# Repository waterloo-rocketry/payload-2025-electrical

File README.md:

2025 Payload Electrical Design
==============================

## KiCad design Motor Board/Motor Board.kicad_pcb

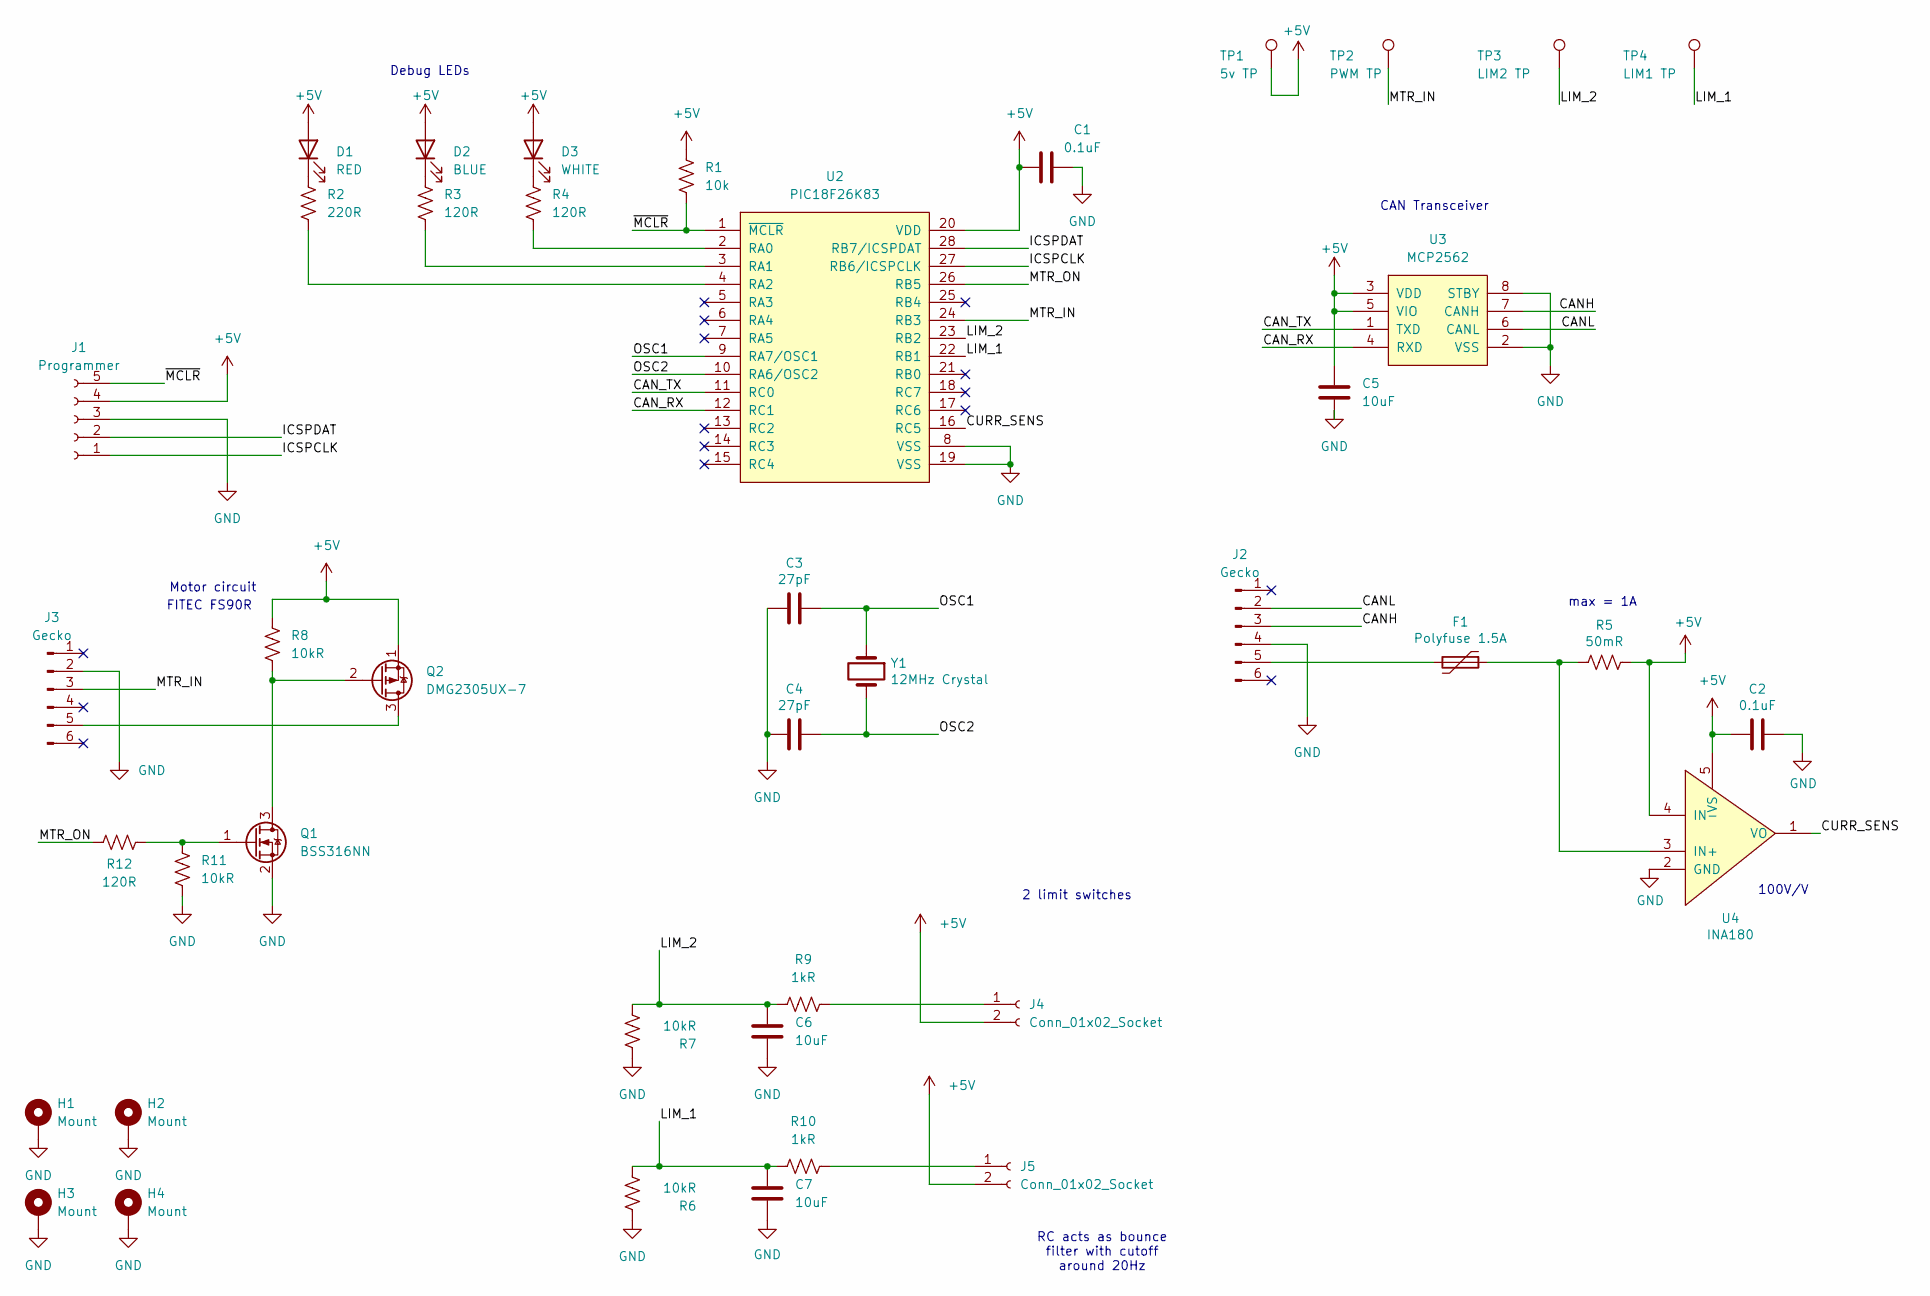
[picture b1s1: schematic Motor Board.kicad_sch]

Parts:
C1, C2: 0.1uF; C_0805_2012Metric_Pad1.18x1.45mm_HandSolder
C3, C4: 27pF; C_0805_2012Metric_Pad1.18x1.45mm_HandSolder; DigiKey 1276-2622-1-ND
C5, C6, C7: 10uF; C_0805_2012Metric_Pad1.18x1.45mm_HandSolder
D1: RED; LED_1206_3216Metric_Pad1.42x1.75mm_HandSolder
D2: BLUE; LED_1206_3216Metric_Pad1.42x1.75mm_HandSolder
D3: WHITE; LED_1206_3216Metric_Pad1.42x1.75mm_HandSolder
F1: Polyfuse 1.5A; Fuse_1206_3216Metric_Pad1.42x1.75mm_HandSolder
H1, H2, H3, H4: Mount; MountingHole_3.2mm_M3_Pad
J1: Programmer; PinSocket_5x2.54_SMD_90deg_952-3198-1-ND
J2, J3: Gecko; connector_Harwin_G125–MG10605M4P
J4, J5: Conn_01x02_Socket; JST_PH_S2B-PH-K_1x02_P2.00mm_Horizontal
Q1: BSS316NN; SOT-323_SC-70_Handsoldering
Q2: DMG2305UX-7; SOT-23
R1: 10k; R_0805_2012Metric_Pad1.20x1.40mm_HandSolder
R2: 220R; R_0805_2012Metric_Pad1.20x1.40mm_HandSolder
R3, R4, R12: 120R; R_0805_2012Metric_Pad1.20x1.40mm_HandSolder
R5: 50mR; R_0805_2012Metric_Pad1.20x1.40mm_HandSolder
R6, R7, R8, R11: 10kR; R_0805_2012Metric_Pad1.20x1.40mm_HandSolder
R9, R10: 1kR; R_0805_2012Metric_Pad1.20x1.40mm_HandSolder
TP1: 5v TP; TestPoint_Pad_1.5x1.5mm
TP2: PWM TP; TestPoint_Pad_1.5x1.5mm
TP3: LIM2 TP; TestPoint_Pad_1.5x1.5mm
TP4: LIM1 TP; TestPoint_Pad_1.5x1.5mm
U2: PIC18F26K83; SOIC-28W_7.5x18.7mm_P1.27mm; DigiKey PIC18LF26K83T-I/SOCT-ND
U3: MCP2562; SOIC-8_3.9x4.9mm_P1.27mm
U4: INA180; SOT-23-5_HandSoldering
Y1: 12MHz Crystal; Crystal_HC49-4H_Vertical; DigiKey 535-9869-1-ND

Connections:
+5V: C1.1, C2.2, C5.1, D1.2 (A), D2.2 (A), D3.2 (A), J1.4, J4.2, J5.2, Q2.1 (S), R1.1, R5.1, R8.1, TP1.1, U2.20 (VDD), U3.3 (VDD), U3.5 (VIO), U4.4 (IN-), U4.5 (VS)
/CANH: J2.3, U3.7 (CANH)
/CANL: J2.2, U3.6 (CANL)
/CAN_RX: U2.12 (RC1), U3.4 (RXD)
/CAN_TX: U2.11 (RC0), U3.1 (TXD)
/CURR_SENS: U2.16 (RC5), U4.1 (VO)
/ICSPCLK: J1.1, U2.27 (RB6/ICSPCLK)
/ICSPDAT: J1.2, U2.28 (RB7/ICSPDAT)
/LIM_1: C7.1, R6.1, R10.2, TP4.1, U2.22 (RB1)
/LIM_2: C6.1, R7.1, R9.2, TP3.1, U2.23 (RB2)
/MTR_IN: J3.3, TP2.1, U2.24 (RB3)
/MTR_ON: R12.1, U2.26 (RB5)
/OSC1: C3.1, U2.9 (RA7/OSC1), Y1.1
/OSC2: C4.1, U2.10 (RA6/OSC2), Y1.2
/~MCLR: J1.5, R1.2, U2.1 (~MCLR)
GND: C1.2, C2.1, C3.2, C4.2, C5.2, C6.2, C7.2, H1.1, H2.1, H3.1, H4.1, J1.3, J2.4, J3.2, Q1.2 (S), R6.2, R7.2, R11.2, U2.8 (VSS), U2.19 (VSS), U3.2 (VSS), U3.8 (STBY), U4.2 (GND)
unnamed: D1.1 (K), R2.1
unnamed: D2.1 (K), R3.1
unnamed: D3.1 (K), R4.1
unnamed: F1.2, J2.5
unnamed: J3.5, Q2.3 (D)
unnamed: J4.1, R9.1
unnamed: J5.1, R10.1
unnamed: Q1.3 (D), Q2.2 (G), R8.2
unnamed: Q1.1 (G), R11.1, R12.2
unnamed: R4.2, U2.2 (RA0)
unnamed: R3.2, U2.3 (RA1)
unnamed: R2.2, U2.4 (RA2)
unnamed: F1.1, R5.2, U4.3 (IN+)

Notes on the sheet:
100V/V
2 limit switches
Debug LEDs
CAN Transceiver
RC acts as bounce filter with cutoff around 20Hz
Motor circuit
FITEC FS90R
max = 1A

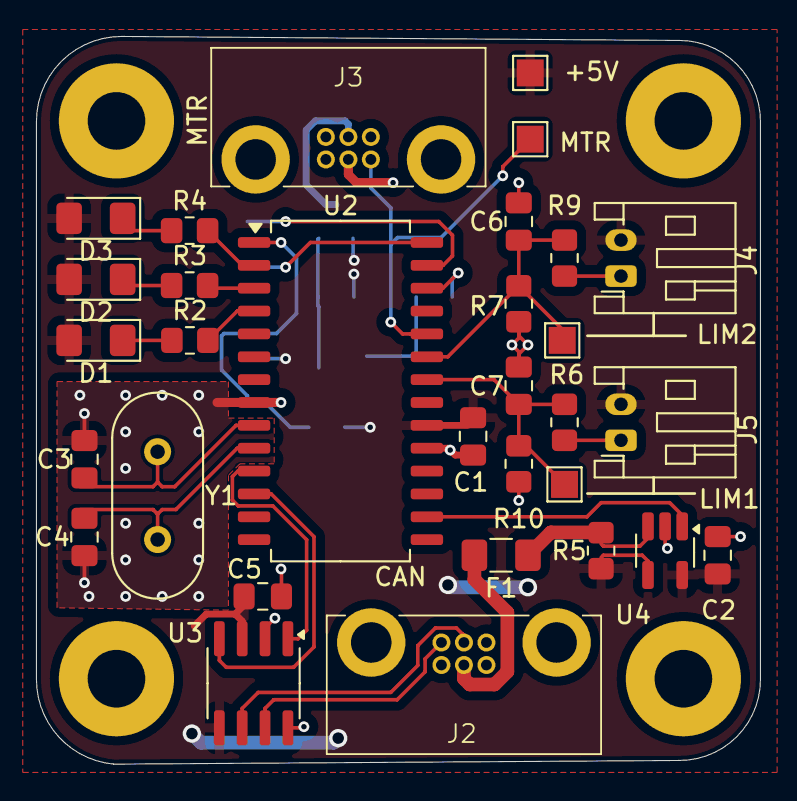
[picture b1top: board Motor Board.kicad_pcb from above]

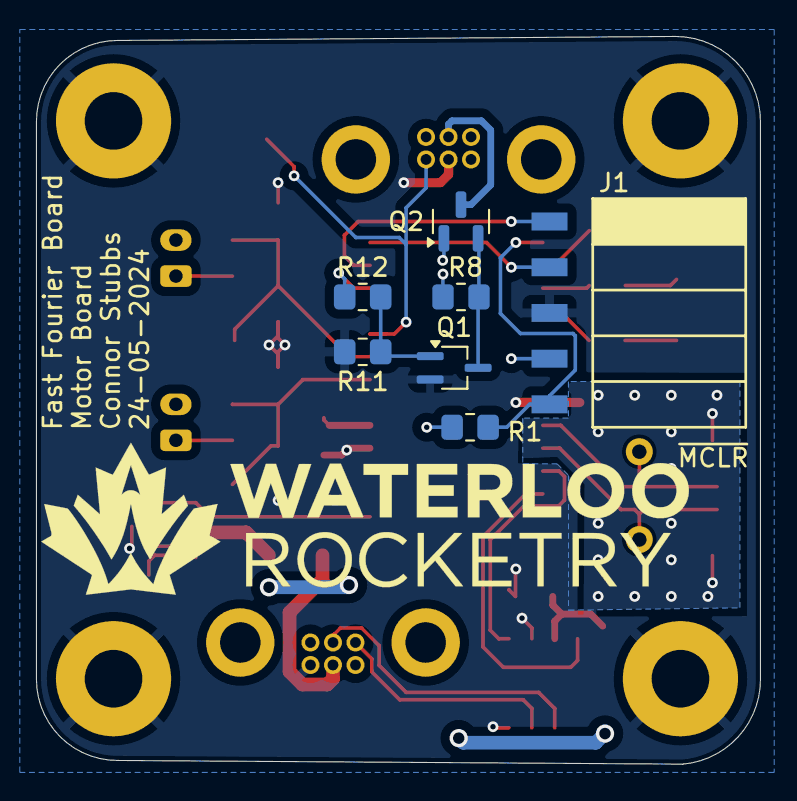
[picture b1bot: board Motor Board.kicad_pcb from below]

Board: 2 copper layers, 40.2 x 40.4 mm, 42 parts (7 on the bottom side), 29 nets.

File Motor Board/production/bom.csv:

Designator,Footprint,Quantity,Value,LCSC Part #
"C1, C2",0805,2,0.1uF,
"C3, C4",0805,2,27pF,
"C5, C6, C7",0805,3,10uF,
D1,1206,1,RED,
D2,1206,1,BLUE,
D3,1206,1,WHITE,
F1,1206,1,Polyfuse 1.5A,
"H1, H2, H3, H4",MountingHole_3.2mm_M3_Pad,4,Mount,
J1,PinSocket_5x2.54_SMD_90deg_952-3198-1-ND,1,Programmer,
"J2, J3",connector_Harwin_G125–MG10605M4P,2,Gecko,
"J4, J5",JST_PH_S2B-PH-K_1x02_P2.00mm_Horizontal,2,Conn_01x02_Socket,
Q1,SOT-323_SC-70_Handsoldering,1,BSS316NN,
Q2,SOT-23,1,DMG2305UX-7,
R1,0805,1,10k,
"R10, R9",0805,2,1kR,
"R11, R6, R7, R8",0805,4,10kR,
"R12, R3, R4",0805,3,120R,
R2,0805,1,220R,
R5,0805,1,50mR,
TP1,TestPoint_Pad_1.5x1.5mm,1,5v TP,
TP2,TestPoint_Pad_1.5x1.5mm,1,PWM TP,
TP3,TestPoint_Pad_1.5x1.5mm,1,LIM2 TP,
TP4,TestPoint_Pad_1.5x1.5mm,1,LIM1 TP,
U2,SOIC-28W_7.5x18.7mm_P1.27mm,1,PIC18F26K83,
U3,SOIC-8_3.9x4.9mm_P1.27mm,1,MCP2562,
U4,SOT-23-5_HandSoldering,1,INA180,
Y1,Crystal_HC49-4H_Vertical,1,12MHz Crystal,

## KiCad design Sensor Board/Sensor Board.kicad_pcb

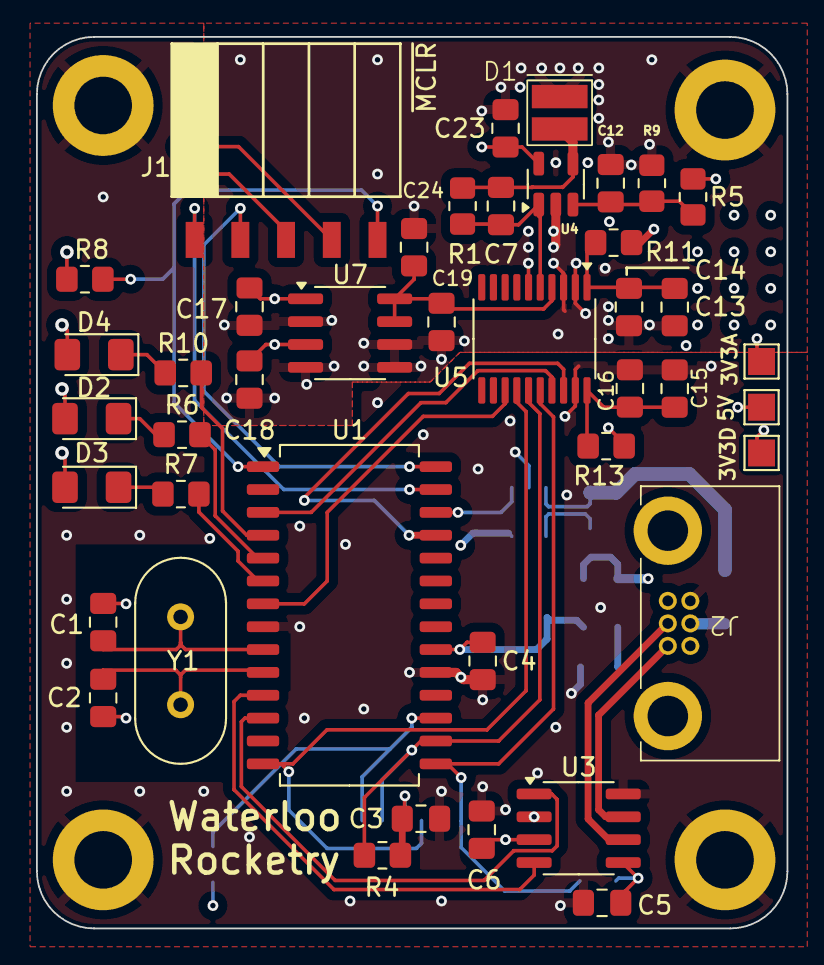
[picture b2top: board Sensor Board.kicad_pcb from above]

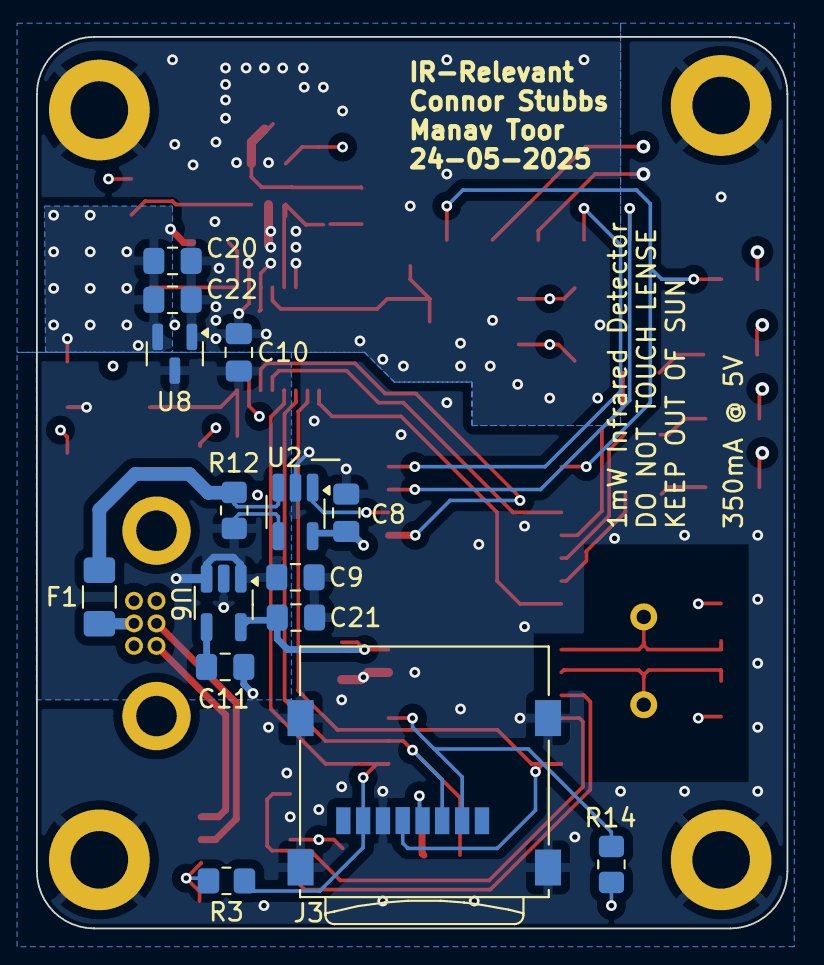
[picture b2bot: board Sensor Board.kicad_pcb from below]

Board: 4 copper layers, 41.7 x 49.5 mm, 61 parts (15 on the bottom side), 37 nets.

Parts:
3V3A: 3V3A; TestPoint_Pad_1.5x1.5mm
3V3D: 3V3D; TestPoint_Pad_1.5x1.5mm
5V: 5v; TestPoint_Pad_1.5x1.5mm
C1, C2: 27pF; C_0805_2012Metric_Pad1.18x1.45mm_HandSolder
C3: 4.7uF; C_0805_2012Metric_Pad1.18x1.45mm_HandSolder
C4, C5, C8, C10, C13, C14, C15, C16, C17, C20, C23: 0.1uF; C_0805_2012Metric_Pad1.18x1.45mm_HandSolder
C6, C22, C24: 10uF; C_0805_2012Metric_Pad1.18x1.45mm_HandSolder
C7: 4.7pF; C_0805_2012Metric_Pad1.18x1.45mm_HandSolder
C9, C12, C21: 1uF; C_0805_2012Metric_Pad1.18x1.45mm_HandSolder
C11: 10nF; C_0805_2012Metric_Pad1.18x1.45mm_HandSolder
C18, C19: 2.2uF; C_0805_2012Metric_Pad1.18x1.45mm_HandSolder
D1: P16612-011CA
D2: RED; LED_1206_3216Metric_Pad1.42x1.75mm_HandSolder
D3: GREEN; LED_1206_3216Metric_Pad1.42x1.75mm_HandSolder
D4: BLUE; LED_1206_3216Metric_Pad1.42x1.75mm_HandSolder
F1: 350mA Polyfuse; Fuse_1206_3216Metric_Pad1.42x1.75mm_HandSolder
H1, H2, H3, H4: MountingHole_Pad; MountingHole_3.2mm_M3_DIN965_Pad
J1: Programming Header; PinSocket_5x2.54_SMD_90deg_952-3198-1-ND
J2: CAN Bus Connector; connector_Harwin_G125–MG10605M4P
J3: Micro_SD_Card; microSD_Molex_WM6698CT-ND
R1: 3.2M; R_0805_2012Metric_Pad1.20x1.40mm_HandSolder
R3, R4, R8, R14: 10kR; R_0805_2012Metric_Pad1.20x1.40mm_HandSolder
R5: 9.31k; R_0805_2012Metric_Pad1.20x1.40mm_HandSolder
R6, R7: 150R; R_0805_2012Metric_Pad1.20x1.40mm_HandSolder
R9: 287R; R_0805_2012Metric_Pad1.20x1.40mm_HandSolder
R10: 90R; R_0805_2012Metric_Pad1.20x1.40mm_HandSolder
R11, R13: 10R; R_0805_2012Metric_Pad1.20x1.40mm_HandSolder
R12: 93.1mR; R_0805_2012Metric_Pad1.20x1.40mm_HandSolder
U1: PIC18F26K83; SOIC-28W_7.5x18.7mm_P1.27mm
U2: INA180; SOT-23-5_HandSoldering
U3: MCP2562; SOIC-8_3.9x4.9mm_P1.27mm
U4: OPA323; SOT-23-5
U5: MCP3561-E/ST; TSSOP-20_4.4x6.5mm_P0.65mm
U6: SPX3819M5-L-3-3; SOT-23-5_HandSoldering
U7: MCP1501-30xSN; SOIC-8_3.9x4.9mm_P1.27mm
U8: MCP1754S-3302xCB; SOT-23
Y1: 12MHz Crystal; Crystal_HC49-4H_Vertical

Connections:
+3V3A: 3V3A.1, C17.1, C18.1, C20.1, C22.1, C23.1, R5.1, R11.1, U4.5 (V+), U7.1 (VDD), U7.3 (~SHDN), U8.2 (VO)
+3V3D: 3V3D.1, C3.2, C4.1, C5.2, C8.1, C21.1, J1.4, J3.4 (VDD), R3.1, R4.1, R8.1, R13.1, R14.1, U1.20 (VDD), U2.5 (VS), U3.5 (VIO), U6.5 (OUT)
+5V: 5V.1, C6.2, C9.1, C10.1, D2.2 (A), D3.2 (A), D4.2 (A), R12.1, U2.4 (IN-), U3.3 (VDD), U6.1 (IN), U6.3 (EN), U8.3 (VI)
/CANH: J2.3, U3.7 (CANH)
/CANL: J2.2, U3.6 (CANL)
/CANRX: U1.11 (RC0), U3.4 (RXD)
/CANTX: U1.12 (RC1), U3.1 (TXD)
/CS_ADC: U1.7 (RA5), U5.13 (*CS)
/CS_SD: J3.2 (DAT3/CD), R14.2, U1.17 (RC6)
/CURR_SENSE: U1.26 (RB5), U2.1 (VO)
/ICSPCLK: J1.1, U1.27 (RB6/ICSPCLK)
/ICSPDAT: J1.2, U1.28 (RB7/ICSPDAT)
/IRQ/MDAT: U1.3 (RA1), U5.17 (*IRQ/MDAT)
/MCLKIN: U1.25 (RB4), U5.18 (MCLKIN)
/MISO: J3.7 (DAT0), R3.2, U1.15 (RC4), U5.16 (SDO)
/MOSI: J3.3 (CMD), R4.2, U1.16 (RC5), U5.15 (SDI)
/OSC1: C1.1, U1.9 (RA7/OSC1), Y1.1
/OSC2: C2.1, U1.10 (RA6/OSC2), Y1.2
/SCLK: J3.5 (CLK), U1.14 (RC3), U5.14 (SCK)
/~MCLR: J1.5, R8.2, U1.1 (~MCLR)
AGND: C10.2, C12.1, C13.1, C14.1, C17.2, C18.2, C19.2, C20.2, C22.2, C23.2, C24.2, D1.1 (K), H1.1, R9.1, U4.2 (V-), U5.2 (AGND), U5.3 (REFIN-), U5.6 (CH1), U7.2 (GND), U7.4 (GND), U7.5 (GND), U7.6 (GND), U8.1 (GND)
GND: C1.2, C2.2, C3.1, C4.2, C5.1, C6.1, C8.2, C9.2, C11.2, C15.2, C16.2, C21.2, H2.1, H3.1, H4.1, J1.3, J2.4, J3.6 (VSS), J3.9 (SHIELD), U1.8 (VSS), U1.19 (VSS), U2.2 (GND), U3.2 (VSS), U3.8 (STBY), U5.19 (DGND), U6.2 (GND)
unnamed: C7.1, D1.2 (A), R1.1, U4.4 (-)
unnamed: D2.1 (K), R6.1
unnamed: D3.1 (K), R7.1
unnamed: D4.1 (K), R10.1
unnamed: F1.1, J2.5
unnamed: R10.2, U1.4 (RA2)
unnamed: R6.2, U1.5 (RA3)
unnamed: R7.2, U1.6 (RA4)
unnamed: F1.2, R12.2, U2.3 (IN+)
unnamed: C12.2, R5.2, R9.2, U4.3 (+)
unnamed: C13.2, C14.2, R11.2, U5.1 (AVDD)
unnamed: C7.2, R1.2, U4.1, U5.5 (CH0)
unnamed: C15.1, C16.1, R13.2, U5.20 (DVDD)
unnamed: C19.1, C24.1, U5.4 (REFIN+), U7.7 (OUT), U7.8 (FB)
unnamed: C11.1, U6.4 (BP)

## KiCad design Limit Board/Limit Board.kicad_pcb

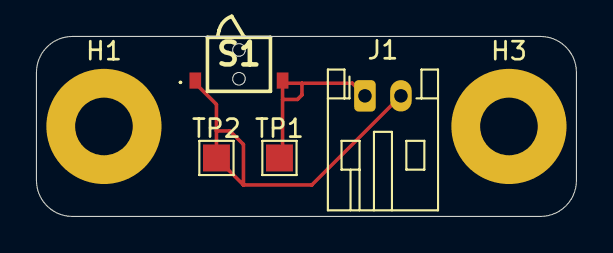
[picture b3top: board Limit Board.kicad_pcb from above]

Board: 2 copper layers, 30.0 x 10.0 mm, 6 parts (0 on the bottom side), 2 nets.

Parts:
H1, H3: Mount; MountingHole_3.2mm_M3_Pad
J1: Conn_01x02_Socket; JST_PH_S2B-PH-K_1x02_P2.00mm_Horizontal
S1: HDS001R
TP1, TP2: TestPoint; TestPoint_Pad_1.5x1.5mm

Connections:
unnamed: J1.1, S1.B1 (N.O.), TP1.1
unnamed: J1.2, S1.A1 (COM), TP2.1

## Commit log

2024-09-12 Initial commit
    Add README.md
2024-09-12 Add Waterloo Rocketry KiCAD footprint submodule
2025-01-28 Add boards
2025-01-31 Finish schematics and footprint assignments
2025-01-31 Fix unneeded thingy thang on limit
2025-01-31 Add osc to motor
2025-01-31 Change 3.3v on sensor
2025-02-01 fix labels
2025-02-02 Add only one board
2025-02-02 add only motor board
2025-02-02 add only sensor board
2025-02-13 Fix comments from review
2025-02-13 Push motor
2025-02-13 Fix edge cuts
2025-03-01 Fix review items
2025-03-05 Switch op amp
2025-03-08 Forgot to push, fix mosfets
2025-03-14 Fix the traces and comments from Pranav
2025-05-17 Cooked another layout-Pranav
2025-05-24 updated optics front end
2025-05-24 added footprints. Custom footprint for photodiode
2025-05-24 fixed footprints not loading
2025-05-24 did layout
2025-05-24 redit layout
2025-05-24 connected grounds
2025-05-24 Add lil limit board (#4)
2025-06-04 implemented Joe's comments
2025-06-04 implemented Joes changes
2025-06-07 Final PCB touches; gerbs
2025-06-07 Polish PCB; gerbs
2025-06-07 removed random 3v3 plane left behine and reconnected grunds
2025-06-07 generated gerbers and drill files
2025-06-07 created schematic pdf
2025-06-07 Add motor board (#3)
2025-06-08 My hideous attemp at fixing merge conflicts
    someone more experienced with git pls help. For some reason the motor branch added files to the "Sensor Board" directory which is cereating merge conflicts.
    My plan is to delete all files in "Sensor Board" so i can try to push again
2025-06-08 My hideous attemp at fixing merge conflicts (#5)
2025-06-08 Add Sensor Board (#2)
